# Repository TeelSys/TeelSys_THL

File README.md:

# TeelSys_THL
ATtiny85 Raspberry Pi Temperature Humidity Light Sensor

View the [GitHub Pages](http://teelsys.github.io/TeelSys_THL/) for this project.

More information regarding this project may be found on the [teelsys.com](http://teelsys.com) blog. Specific entries for this project include the following:

* [I2C Communications between Raspberry Pi and Arduino  Part One](http://teelsys.com/?p=244)
* [I2C Communications between Raspberry Pi and Arduino  Part Two](http://teelsys.com/?p=265)
* [I2C Communications between Raspberry Pi and Arduino  Part Three](http://teelsys.com/?p=314)
* [I2C Communications between Raspberry Pi and Arduino  Part Four](http://teelsys.com/?p=332)
* [I2C Communications between Raspberry Pi and Arduino  Update, BOM, and Source Control](http://teelsys.com/?p=393)

## Release Notes
### Version 0.1.0 - 21 March 2016
* Stable for up to three I2C devices
* Uses the PIGPIO library to bit bang the I2C bus (REF: http://abyz.co.uk/rpi/pigpio/pdif2.html)
* Documentation should be able to get anyone up and running with this version

#### TODO
* Writeup complete documentation from start to finish
  * Add documentation Raspberry Pi Hat (Not a true hat as there is no flash)
  * Add more detailed design documentation 

### Version 0.0.1 - 19 March 2016
* Stable for one I2C device only
* Uses the Raspberry Pi I2C hardware control

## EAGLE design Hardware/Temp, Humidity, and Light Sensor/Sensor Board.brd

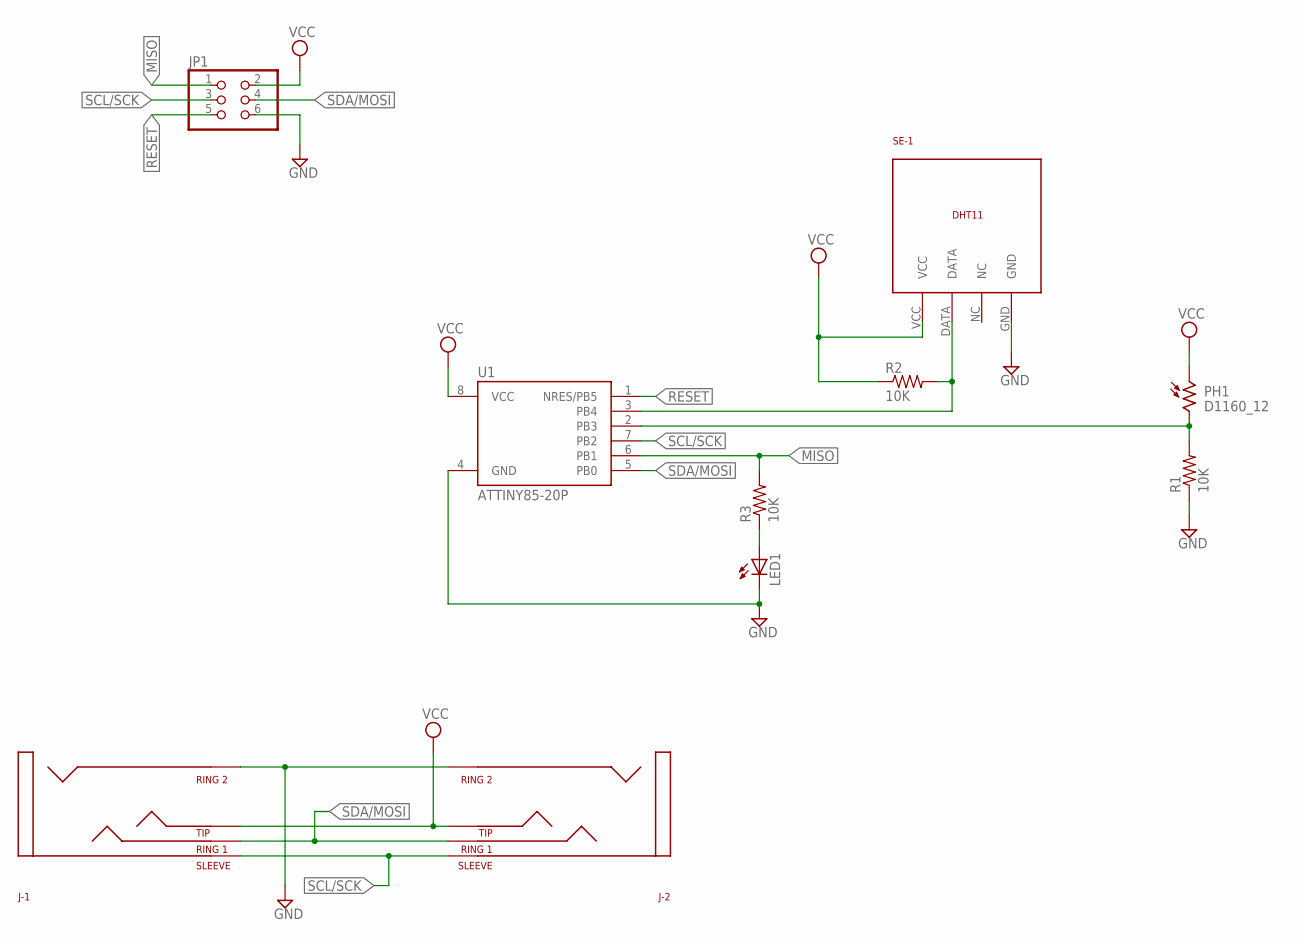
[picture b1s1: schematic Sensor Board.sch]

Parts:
J-1, J-2: 4POLE_AUDIO_JACK
JP1: PINHD-2X3; 2X03
LED1: LED5MM
PH1: D1160_12; D11XX
R1, R2, R3: 10K; 0805-THM
SE-1: DHT11THROUGH_HOLE; DHT11
U1: ATTINY85-20P; PDIP08_300MIL

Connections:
GND: J-1.RING2, J-2.RING2, JP1.6, LED1.K (C), R1.1, SE-1.GND, U1.4 (GND)
MISO: JP1.1, R3.2, U1.6 (PB1)
unnamed: PH1.2, R1.2, U1.2 (PB3)
unnamed: R2.2, SE-1.DATA, U1.3 (PB4)
unnamed: LED1.A, R3.1
RESET: JP1.5, U1.1 (NRES/PB5)
SCL/SCK: J-1.SLEEVE, J-2.SLEEVE, JP1.3, U1.7 (PB2)
SDA/MOSI: J-1.RING1, J-2.RING1, JP1.4, U1.5 (PB0)
VCC: J-1.TIP1 (TIP), J-2.TIP1 (TIP), JP1.2, PH1.1, R2.1, SE-1.VCC, U1.8 (VCC)

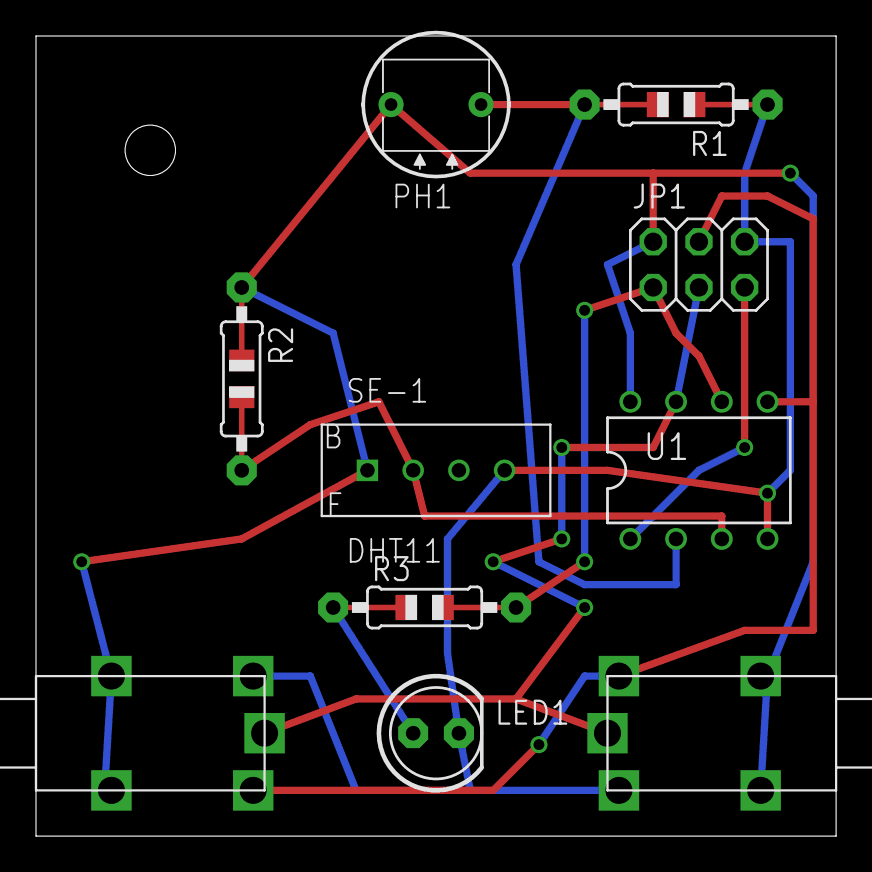
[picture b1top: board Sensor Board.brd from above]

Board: 2 copper layers, 44.5 x 44.5 mm, 10 parts (0 on the bottom side), 9 nets.

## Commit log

2016-03-19 Create gh-pages branch via GitHub
2016-03-19 Initial File Load
2016-03-19 Adding files for the case
2016-03-19 Added BOM
2016-03-19 Updated README.md to include links to the blog
2016-03-19 Corrected link to the TeelSys website
2016-03-19 Testing GitHub Pages
2016-03-19 Added link to the GitHub Pages site
2016-03-19 Updated the README.mdfile to contain some useful information such as links to the blog
2016-03-20 Fixed line endings which were corrupted by Git.
    Added some missing and new files as well.
2016-03-20 Added Release Notes
2016-03-20 Updated documentation and added missing setupgpio.sh file
2016-03-22 * Stable for up to three I2C devices * Uses the PIGPIO library to bit bang the I2C bus (REF: http://abyz.co.uk/rpi/pigpio/pdif2.html) * Documentation should be able to get anyone up and running with 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
2016-03-22 Fixed TODO Header (Maybe)
2016-03-22 Second try
2016-03-22 Another attempt
2016-03-25 Address was not set to match the thl.py script.
